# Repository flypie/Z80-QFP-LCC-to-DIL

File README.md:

# Z80-QFP-LCC-to-DIL

Convert LCC or QFP Z80s to DIL pin out. Also could be used to connect LCC or QFP to breadboard or withthe right sized pins, connect to breadboard and give lablled pins for testing.

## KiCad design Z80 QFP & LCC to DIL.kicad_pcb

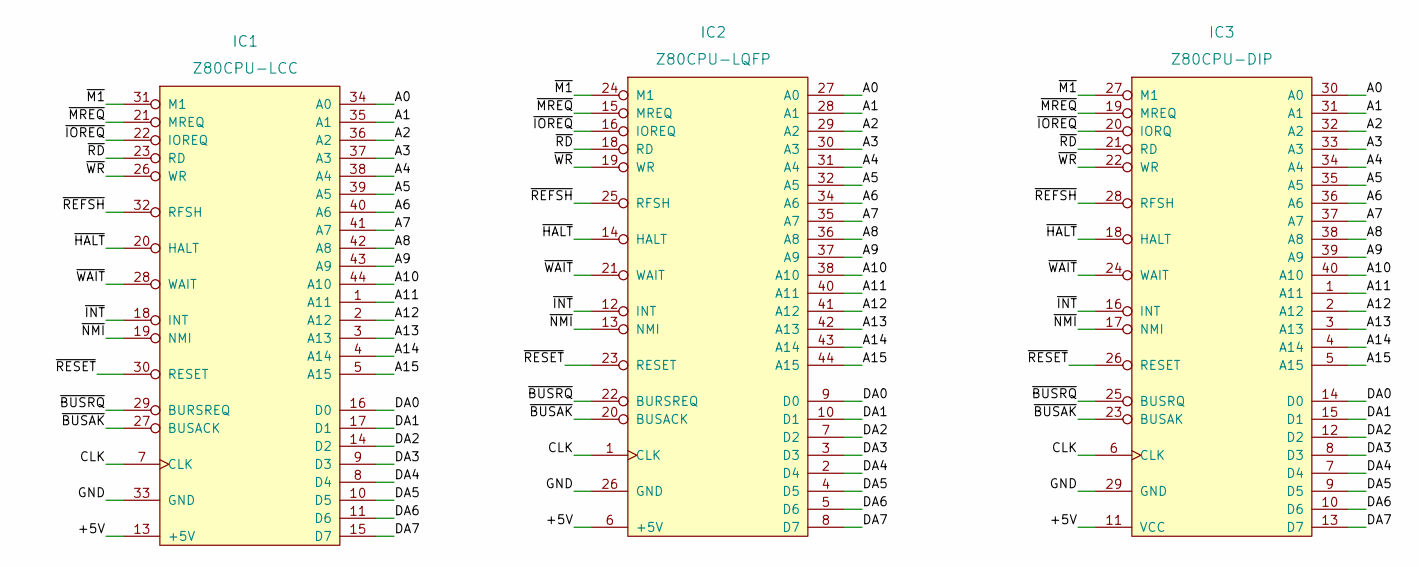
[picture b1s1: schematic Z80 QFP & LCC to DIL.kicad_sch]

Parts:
IC1: Z80CPU-LCC; PLCC-44_THT-Socket; Manufacturer_Part_Number Z84C00
IC2: Z80CPU-LQFP; LQFP-44_10x10mm_P0.8mm
IC3: Z80CPU-DIP; DIP-40_W15.24mm

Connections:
/+5V: IC1.13 (+5V), IC2.6 (+5V), IC3.11 (VCC)
/A0: IC1.34 (A0), IC2.27 (A0), IC3.30 (A0)
/A1: IC1.35 (A1), IC2.28 (A1), IC3.31 (A1)
/A2: IC1.36 (A2), IC2.29 (A2), IC3.32 (A2)
/A3: IC1.37 (A3), IC2.30 (A3), IC3.33 (A3)
/A4: IC1.38 (A4), IC2.31 (A4), IC3.34 (A4)
/A5: IC1.39 (A5), IC2.32 (A5), IC3.35 (A5)
/A6: IC1.40 (A6), IC2.34 (A6), IC3.36 (A6)
/A7: IC1.41 (A7), IC2.35 (A7), IC3.37 (A7)
/A8: IC1.42 (A8), IC2.36 (A8), IC3.38 (A8)
/A9: IC1.43 (A9), IC2.37 (A9), IC3.39 (A9)
/A10: IC1.44 (A10), IC2.38 (A10), IC3.40 (A10)
/A11: IC1.1 (A11), IC2.40 (A11), IC3.1 (A11)
/A12: IC1.2 (A12), IC2.41 (A12), IC3.2 (A12)
/A13: IC1.3 (A13), IC2.42 (A13), IC3.3 (A13)
/A14: IC1.4 (A14), IC2.43 (A14), IC3.4 (A14)
/A15: IC1.5 (A15), IC2.44 (A15), IC3.5 (A15)
/CLK: IC1.7 (CLK), IC2.1 (CLK), IC3.6 (CLK)
/DA0: IC1.16 (D0), IC2.9 (D0), IC3.14 (D0)
/DA1: IC1.17 (D1), IC2.10 (D1), IC3.15 (D1)
/DA2: IC1.14 (D2), IC2.7 (D2), IC3.12 (D2)
/DA3: IC1.9 (D3), IC2.3 (D3), IC3.8 (D3)
/DA4: IC1.8 (D4), IC2.2 (D4), IC3.7 (D4)
/DA5: IC1.10 (D5), IC2.4 (D5), IC3.9 (D5)
/DA6: IC1.11 (D6), IC2.5 (D6), IC3.10 (D6)
/DA7: IC1.15 (D7), IC2.8 (D7), IC3.13 (D7)
/GND: IC1.33 (GND), IC2.26 (GND), IC3.29 (GND)
/~BUSAK: IC1.27 (BUSACK), IC2.20 (BUSACK), IC3.23 (BUSAK)
/~BUSRQ: IC1.29 (BURSREQ), IC2.22 (BURSREQ), IC3.25 (BUSRQ)
/~HALT: IC1.20 (HALT), IC2.14 (HALT), IC3.18 (HALT)
/~INT: IC1.18 (INT), IC2.12 (INT), IC3.16 (INT)
/~IOREQ: IC1.22 (IOREQ), IC2.16 (IOREQ), IC3.20 (IORQ)
/~M1: IC1.31 (M1), IC2.24 (M1), IC3.27 (M1)
/~MREQ: IC1.21 (MREQ), IC2.15 (MREQ), IC3.19 (MREQ)
/~NMI: IC1.19 (NMI), IC2.13 (NMI), IC3.17 (NMI)
/~RD: IC1.23 (RD), IC2.18 (RD), IC3.21 (RD)
/~REFSH: IC1.32 (RFSH), IC2.25 (RFSH), IC3.28 (RFSH)
/~RESET: IC1.30 (RESET), IC2.23 (RESET), IC3.26 (RESET)
/~WAIT: IC1.28 (WAIT), IC2.21 (WAIT), IC3.24 (WAIT)
/~WR: IC1.26 (WR), IC2.19 (WR), IC3.22 (WR)

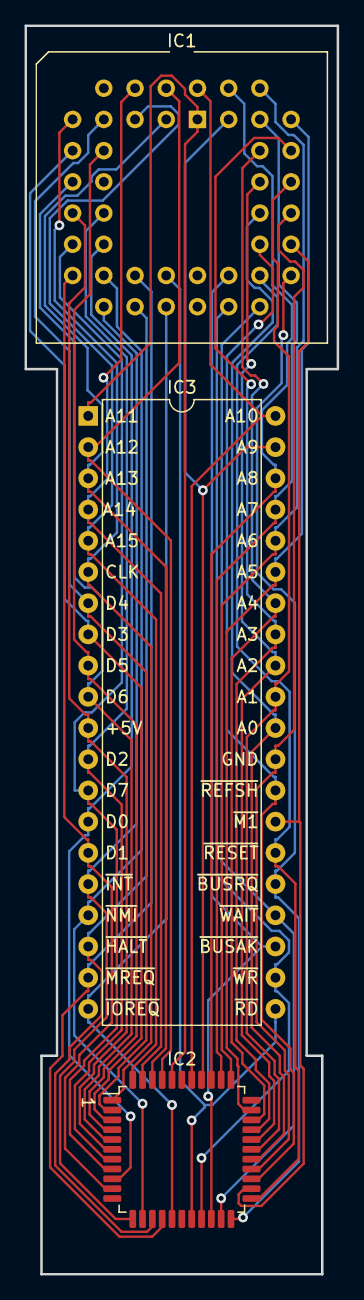
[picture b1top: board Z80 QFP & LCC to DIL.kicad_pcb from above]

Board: 2 copper layers, 25.4 x 101.6 mm, 3 parts (0 on the bottom side), 40 nets.

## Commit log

2022-05-05 add jpg
2022-06-19 Change text for inveted logic pins from ! to ~{}

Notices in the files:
Z80 QFP & LCC to DIL.kicad_pcb:
©John Bradley 2022 Z80 DIL munger V1
